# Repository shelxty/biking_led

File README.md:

## Bikers Alarm: Safety LED & Alert System

This is a safety system created for bikers at night, utilizing a flex PCB that wraps around the arm and opens up 3 LEDs with the push of a button! Have a light on you as you're biking around at night so that cars can see you, and when you're within 5 meters of a person, a buzzer will automatically buzz to alert them of your presence/you of their presence. 

*Created during the Hack Club: Fallout event in Shenzhen, China* 

### Design 

*Schematic* 

*PCB Design* 

*3D View* 

### Bill of Materials 

Reference | Description | Value | Qty | MOQ | Price Per Unit ($) | Total Price ($) | Datasheet | Footprint | MPN | Link
---|---|---|---|---|---|---|---|---|---|---
BT1 | Single-cell battery | Battery_Cell | 1 | 1 | 3.87 | 3.87 | N/A | Battery:BatteryHolder_Keystone_3034_1x20mm | N/A | [Link](https://www.aliexpress.us/item/3256808925172396.html?spm=a2g0o.productlist.main.11.6e1523a2T5o5mT&algo_pvid=a7f5d709-8287-4bd9-877e-4b7454d07aea&algo_exp_id=a7f5d709-8287-4bd9-877e-4b7454d07aea-10&pdp_ext_f=%7B%22order%22%3A%22115%22%2C%22eval%22%3A%221%22%2C%22fromPage%22%3A%22search%22%7D&pdp_npi=6%40dis%21USD%215.38%213.87%21%21%2136.32%2126.15%21%4021032f3717820018898186181ef57d%2112000047954562112%21sea%21US%217756416958%21X%211%210%21n_tag%3A-29911%3Bd%3A882c3b75%3Bm03_new_user%3A-29895&curPageLogUid=gVBhZCgn1w6G&utparam-url=scene%3Asearch%7Cquery_from%3A%7Cx_object_id%3A1005009111487148%7C_p_origin_prod%3A)
BZ1 | Buzzer, polarized | Buzzer | 1 | 10 | 0.0572 | 0.57 | N/A | Buzzer_Beeper:Buzzer_12x9.5RM7.6 | 1207-P6.5MM | [Link](https://www.lcsc.com/product-detail/C49246964.html)
D1,D2,D3 | Light emitting diode | LED | 3 | 20 | 0.022 | 0.44 | N/A | LED_THT:LED_D5.0mm | BAT54,215 | [Link](https://www.lcsc.com/product-detail/C85084.html?s_z=n_q_t_diode&spm=wm.fly.bg.7.xh___wm.ssy.tc.1.tz&lcsc_vid=R1YMUQAHQVVeVlBXQgcPXgZQQFAPU1RVFlkIU1cHQwMxVlNeRFFdX1JfRVVfVTsOAxUeFF5JWBYZEEoKFBINSQcJGk4eFQsCAgIaSgADAwAHC0slQlNdXlxQRU8GEwkK)
R1,R2,R3 | Resistor | 300 | 3 | 100 | 0.0016 | 0.16 | N/A | Resistor_THT:R_Axial_DIN0207_L6.3mm_D2.5mm_P7.62mm_Horizontal | FRC0402J301 TS | [Link](https://www.lcsc.com/product-detail/C2906927.html?s_z=n_q_t_resistor&spm=wm.fly.bg.6.xh___wm.ssy.tc.0.tz&lcsc_vid=R1YMUQAHQVVeVlBXQgcPXgZQQFAPU1RVFlkIU1cHQwMxVlNeRFFdX1xTQFVdXzsOAxUeFF5JWBYZEEoKFBINSQcJGk4eFQsCAgIaSgADAwAHC0slT1ReX1BIHxUDCw%3D%3D)
SW1 | Switch, single pole double throw | SW_SPDT | 1 | 20 | 0.0298 | 0.6 | N/A | N/A | 1TS005F-1600-4301A2-CT | [Link](https://www.lcsc.com/product-detail/C22391231.html?s_z=n_q_t_button&spm=wm.fly.bg.0.xh___wm.ssy.tc.1.tz&lcsc_vid=R1YMUQAHQVVeVlBXQgcPXgZQQFAPU1RVFlkIU1cHQwMxVlNeRFFdXlRQQVFZUTsOAxUeFF5JWBYZEEoKFBINSQcJGk4NBhADEA4cHktQQlBADxALGw%3D%3D)
U1 | 20MHz, 16kB Flash, 2kB SRAM, 256B EEPROM, SOIC-20 | ATtiny1616-S | 1 | 1 | 1.71 | 1.71 | [Link](http://ww1.microchip.com/downloads/en/DeviceDoc/ATtiny3216_ATtiny1616-data-sheet-40001997B.pdf) | Package_SO:SOIC-20W_7.5x12.8mm_P1.27mm | ATTINY1616-SNR | [Link](https://www.lcsc.com/product-detail/C609652.html?s_z=n_q_ATtiny1616-S&spm=wm.fly.bg.4.xh&lcsc_vid=R1YMUQAHQVVeVlBXQgcPXgZQQFAPU1RVFlkIU1cHQwMxVlNeRFFdXlVfTlZdUjsOAxUeFF5JWBYZEEoKFBINSQcJGk4eFQsCAgIaSgADAwAHC0slRVNdXlVURFBADxALGw%3D%3D)
U2 | 5m distance ranging ToF sensor, 3x3 zones, LGA-12 | TMF8820 | 1 | 1 | 11.98 | 11.98 | [Link](https://ams.com/documents/20143/6015057/TMF882X_DS000693_8-00.pdf) | Sensor_Distance:AMS_OLGA12 | TMF8820-1AM | [Link](https://www.lcsc.com/product-detail/C17336360.html?s_z=s_p_TMF8820-1AM&spm=wm.fly.bg.0.xh&lcsc_vid=R1YMUQAHQVVeVlBXQgcPXgZQQFAPU1RVFlkIU1cHQwMxVlNeRFFdXldXRlJdVTsOAxUeFF5JWBYZEEoKFBINSQcJGk4dAgUUFAk%3D)
Total |  |  | 11 |  |  | 19.33 |  |  |  |

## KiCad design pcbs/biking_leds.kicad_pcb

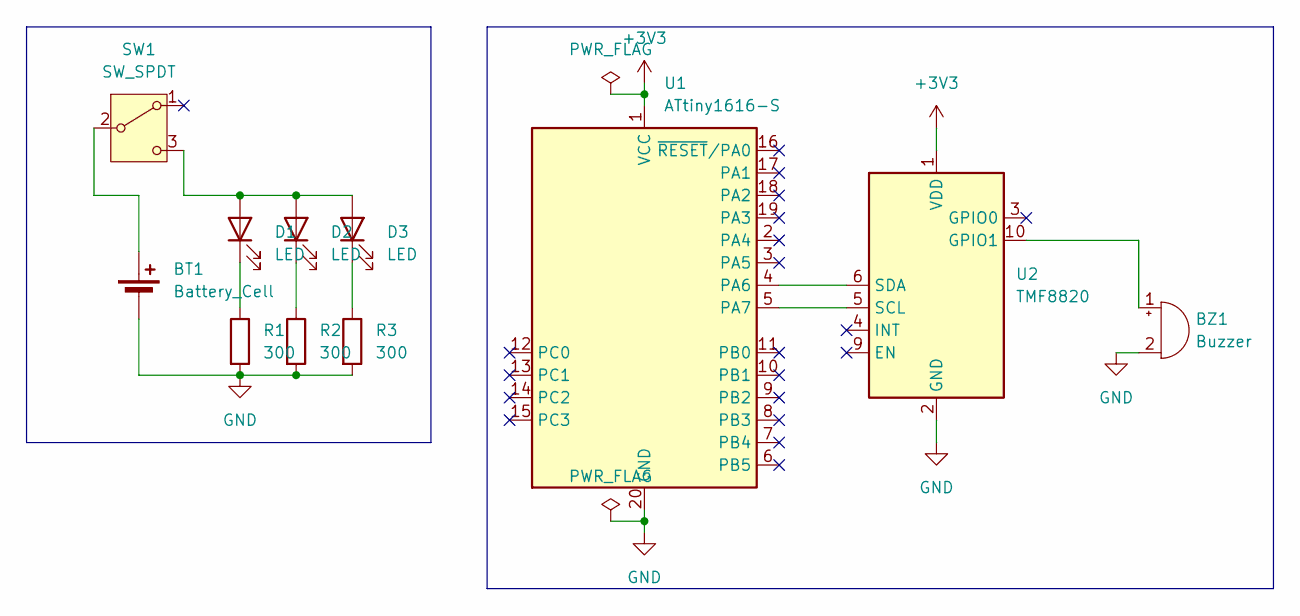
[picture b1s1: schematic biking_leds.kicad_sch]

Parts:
BT1: Battery_Cell; BatteryHolder_Keystone_3034_1x20mm
BZ1: Buzzer; Buzzer_12x9.5RM7.6
D1, D2, D3: LED; LED_D5.0mm
R1, R2, R3: 300; R_Axial_DIN0207_L6.3mm_D2.5mm_P7.62mm_Horizontal
SW1: SW_SPDT
U1: ATtiny1616-S; SOIC-20W_7.5x12.8mm_P1.27mm
U2: TMF8820; AMS_OLGA12

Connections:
+3V3: U1.1 (VCC), U2.1 (VDD), U2.7 (VDD), U2.12 (VDD)
GND: BT1.2 (-), BZ1.2 (-), R1.2, R2.2, R3.2, U1.20 (GND), U2.2 (GND), U2.8 (GND), U2.11 (GND)
unnamed: BT1.1 (+), SW1.2 (B)
unnamed: BZ1.1 (+), U2.10 (GPIO1)
unnamed: D1.2 (A), D2.2 (A), D3.2 (A), SW1.3 (C)
unnamed: D1.1 (K), R1.1
unnamed: D2.1 (K), R2.1
unnamed: D3.1 (K), R3.1
unnamed: U1.4 (PA6), U2.6 (SDA)
unnamed: U1.5 (PA7), U2.5 (SCL)

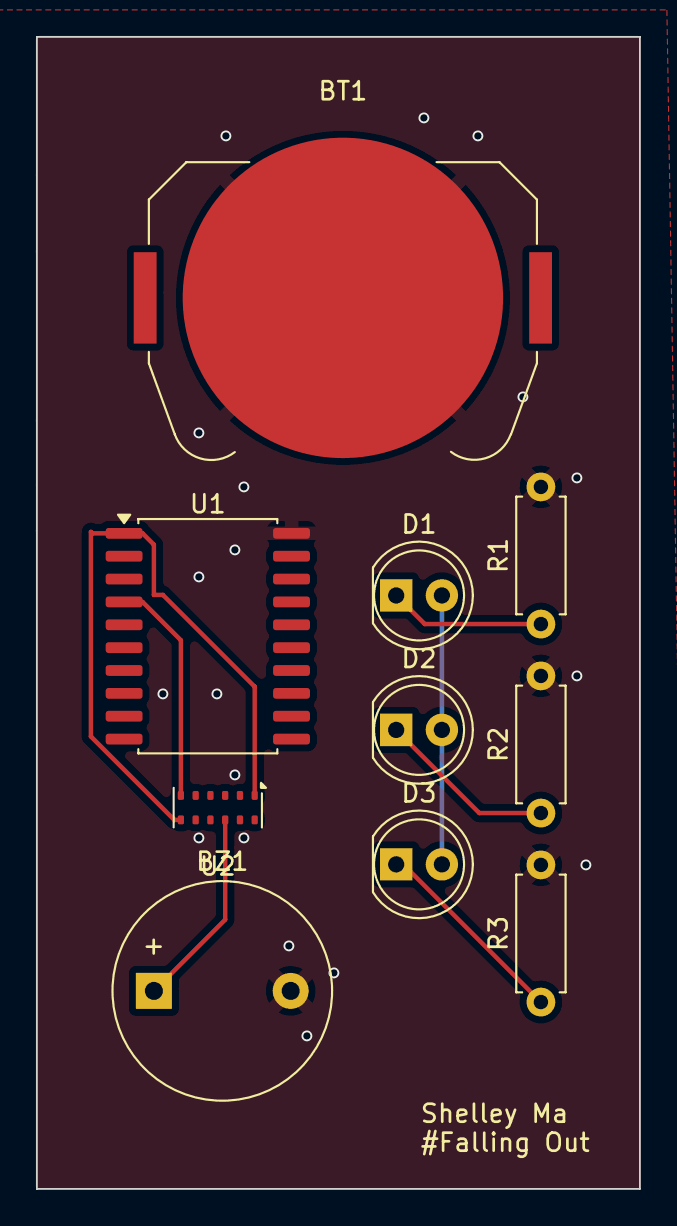
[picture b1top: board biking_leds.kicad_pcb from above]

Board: 2 copper layers, 33.5 x 64.0 mm, 10 parts (0 on the bottom side), 9 nets.
